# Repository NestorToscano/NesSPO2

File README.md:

# SpO₂ Interface Module PCB (KiCad 9)

This repository contains the hardware design for a simple **SpO₂ interface module PCB**, designed in **KiCad 9**. The board serves as a carrier and interconnect for an Arduino-compatible microcontroller, an **SSD1306 OLED display**, a **MAX30102 SpO₂/heart-rate sensor module**, and basic user input components.

The design focuses on clean signal routing, modular integration, and fabrication-ready layout rather than signal processing or firmware implementation.

## Project Overview

The purpose of this board is to provide a compact and organized way to connect common off-the-shelf modules used in SpO₂ prototyping. The PCB primarily functions as an interconnection and mounting platform, integrating passive components and connectors into a single, manufacturable design.

## Features

- Arduino-compatible header connections  
- Interface for **MAX30102 SpO₂ sensor module**  
- Interface for **SSD1306 I²C OLED display**  
- Compact, fabrication-ready PCB layout  

## Repository Contents

- KiCad 9 project files (schematic and PCB)
- PCB layout and routing
- Fabrication-ready Gerber and drill files

All sensing, processing, and display control are intended to be handled by the external microcontroller.

## Tools Used

- **KiCad 9** – schematic capture and PCB layout

## Manufacturing

The included Gerber and drill files are ready for submission to standard PCB fabrication services. The design follows typical clearance and trace-width rules compatible with low-cost fabs.
The design was intended to be used for JLCPCB.

## Intended Use

- SpO₂ and heart-rate prototyping
- Arduino-based biomedical projects

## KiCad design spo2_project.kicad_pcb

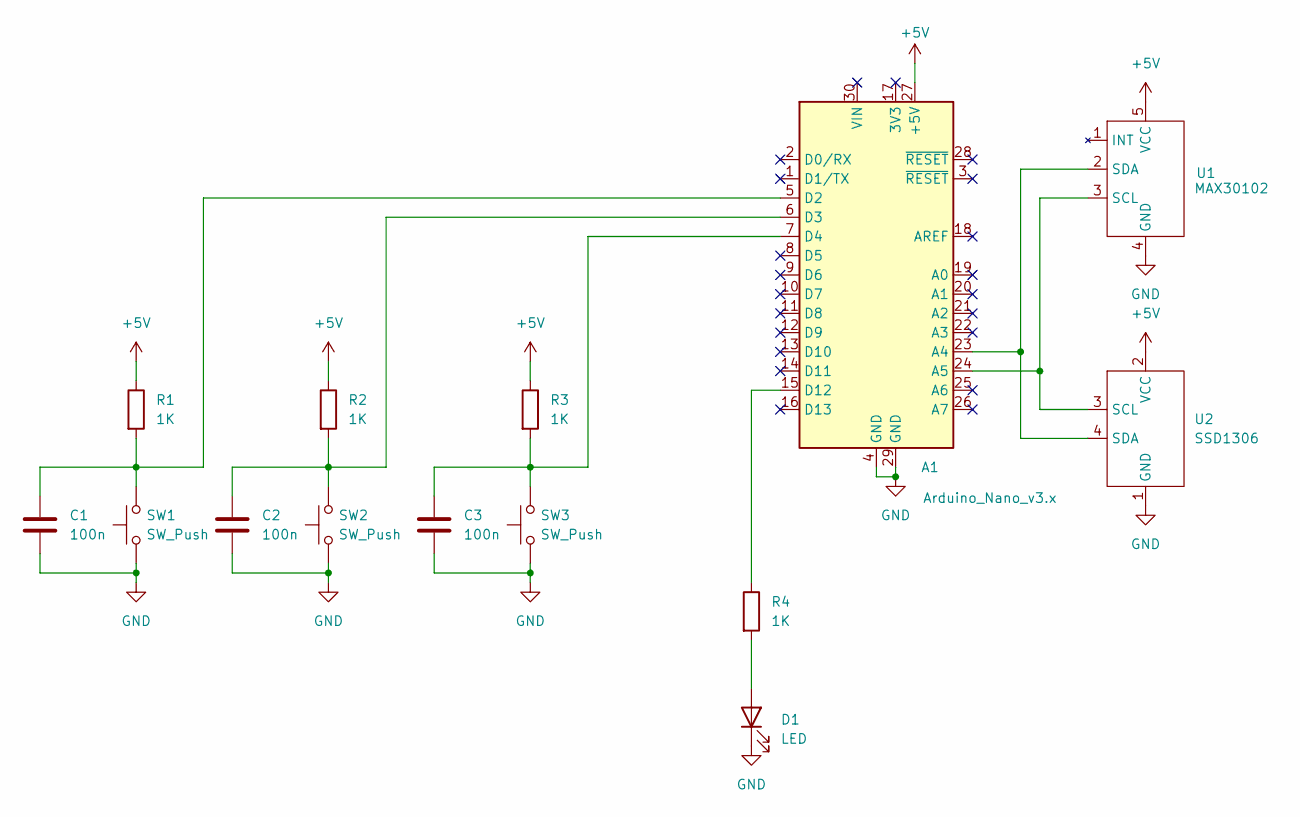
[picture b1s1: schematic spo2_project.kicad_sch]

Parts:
A1: Arduino_Nano_v3.x; Arduino_Nano
C1, C2, C3: 100n; C_Disc_D5.1mm_W3.2mm_P5.00mm
D1: LED; LED_D5.0mm
R1, R2, R3, R4: 1K; R_Axial_DIN0207_L6.3mm_D2.5mm_P7.62mm_Horizontal
SW1, SW2, SW3: SW_Push; SW_PUSH_6mm
U1: MAX30102; MAX30102_MODULE
U2: SSD1306

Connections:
+5V: A1.27 (+5V), R1.1, R2.1, R3.1, U1.5 (VCC), U2.2 (VCC)
GND: A1.4 (GND), A1.29 (GND), C1.2, C2.2, C3.2, D1.1 (K), SW1.1, SW2.1, SW3.1, U1.4 (GND), U2.1 (GND); also elsewhere on the board
unnamed: A1.23 (A4), U1.2 (SDA), U2.4 (SDA)
unnamed: A1.24 (A5), U1.3 (SCL), U2.3 (SCL)
unnamed: A1.5 (D2), C1.1, R1.2, SW1.2
unnamed: A1.6 (D3), C2.1, R2.2, SW2.2
unnamed: A1.7 (D4), C3.1, R3.2, SW3.2
unnamed: A1.15 (D12), R4.1
unnamed 8: D1.2 (A), R4.2; also elsewhere on the board

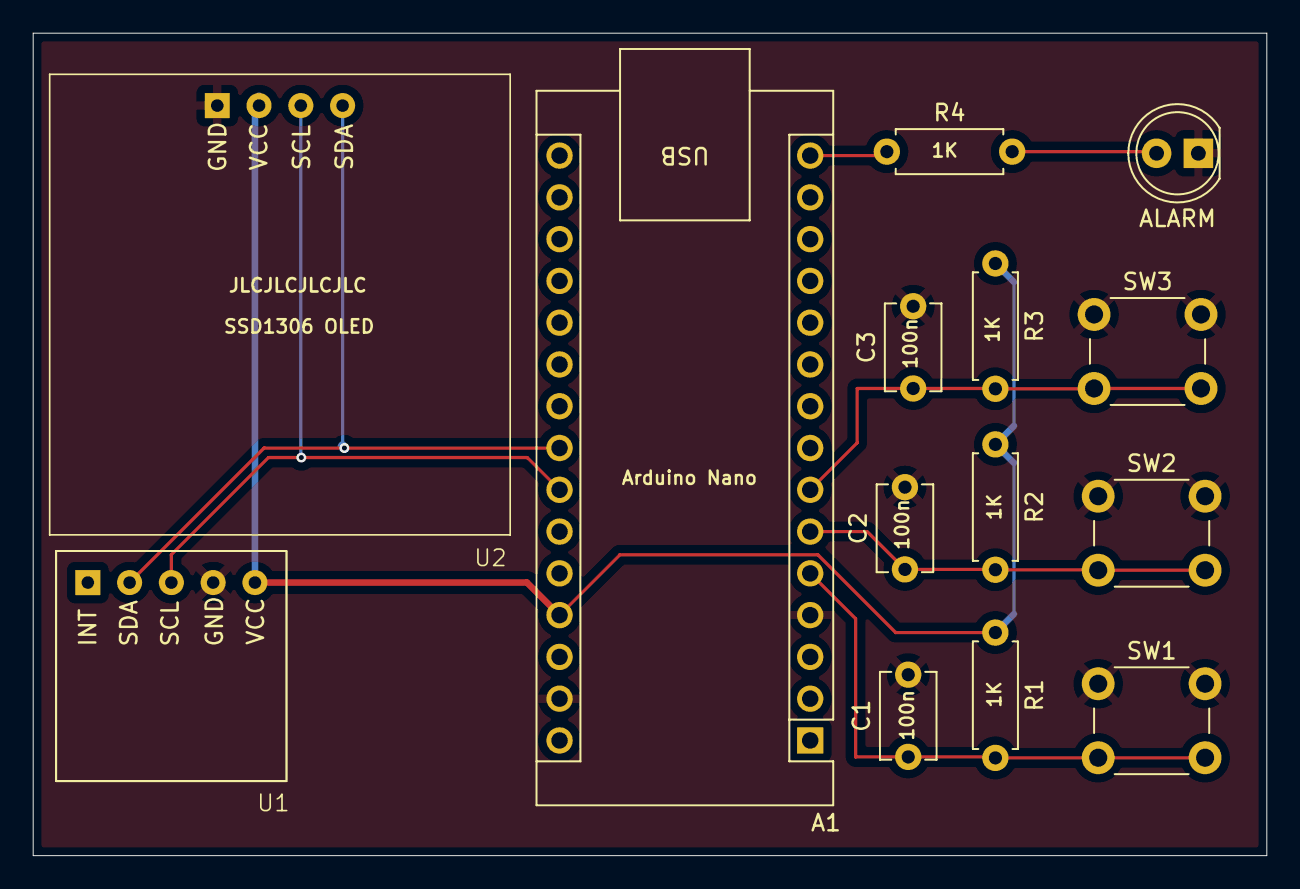
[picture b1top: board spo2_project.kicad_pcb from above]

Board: 4 copper layers, 75.0 x 50.0 mm, 14 parts (0 on the bottom side), 9 nets.

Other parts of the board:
ALARM: LED; LED_D5.0mm

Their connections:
GND: ALARM.1 (K); also elsewhere on the board
unnamed 8: ALARM.2 (A); also elsewhere on the board

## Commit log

2026-01-04 added project files
2026-01-04 removed file
2026-01-04 Add README for SpO₂ Interface Module PCB
    Added detailed project information for SpO₂ interface module PCB, including features, tools used, and intended use.
